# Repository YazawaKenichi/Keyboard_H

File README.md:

# Keyboard_H
This is My First Keyboard Project.

#### 基板とシャーシのデータの完全形
これらのデータで発注・加工する。

#### 自作キーボードの設計
このリポジトリは自作キーボードのためのリポジトリ。
ただしハードウェア設計に関するファイルのみ。うｐ主のインフラの事情的に、ハードは Windows ソフトは Ubuntu で開発することになってしまったので、ハードとソフトでリポジトリを分けた。
統合してぇなぁ...

### 以下全部自己満メモ！自分用れどめ！

##### LED の点灯回路について考える
- USB バスパワー:5V 500mA
- Raspberry Pi Pico の GPIO のパワー
- Raspberry Pi Pico のピンによる電気特性は [RP2040 のデータシート](https://datasheets.raspberrypi.org/rp2040/rp2040-datasheet.pdf) 『5.2.3. Pin Specifications』を参照
- .
- キーボード全体で 300mA になるようにしたい。
- USB 5V だが、実際 500 mA くらい使用すると 4.8V くらいに下がってしまうので、USB デバイスはそうならないように余裕を持たせて設計する。
- GPIO で FET のゲートを制御し、Vbus からの電力を供給する。
- LED と制限抵抗は必ず一つにまとめる。
- .
- 謎があって、USB から電力を入手するとしても、87 個の LED を並列に点灯させようとすると、一つの 抵抗 + LED に流せる電流は最大でも 300 mA / 87 個 ≒ 3.4 mA となってちょっと弱すぎじゃね？って感じがしてしまう。これじゃあ LED 点灯できないじゃん...
- .
- LED のデータシート？これ何？
- output current 出力の最大値 MAX 100 mA
- current limit 制限電流 MIN 150 mA TYP 350 mA MAX 450 mA
- .
- LED の設定
- 一つの LED に電流制限可変抵抗と LED を直列に繋いだ回路において、デューティー比 100% という条件で以下の状態を記録。
- 電源電圧 5 V
- 抵抗降下電圧 1.692 V
- LED 電圧 3.17 V
- 電流 19.30 mA
- 抵抗値 84.5 Ω
- ※小数点以下一桁目より下は当てにならないかも... 0.1 レベルなら当てになるかも。
- 上記が丁度よい輝度になっている。
- .
- 参考までに、電源電圧 3.3 V の時の値も記録しておく。
- 抵抗降下電圧 0.267 V
- LED 電圧 3.03 V
- 電流 10.58 mA
- 抵抗値 21.2 Ω
- ※小数点以下一桁目より下はry
- .
- ついでのついでに参考として、データシートの値を記録しておく。
- デューティー比 100% 電流値  30 mA
- デューティー比 10 % 電流値 100 mA
- 20 mA の時の LED 電圧降下 3.1 V
- .
- 疑問点
- PWM 制御すれば、デューティー比 100 % の時よりも大きな電流を流せるということはわかるけど、推奨デューティー比が 1/10 とかになってて、結局欲しい輝度に届かなくなったりしないのかな？
- Arduino でいいから実験してみると良いかもしれない。
- .
- FET + PWM で実験してみた。
- Nch MOSFET 2N7000 で実験したので、回路的にはローサイド駆動。
- 電流制限抵抗 45Ω PWM: 20ms(50Hz) 100% において、以下を記録。
- 電流 30 mA LED 降下電圧 3.5 V 抵抗降下電圧 1.46 V 但し、100% では僅かに発熱したため、100% 以下での駆動を推奨する。
- .
- なんかもうぐちゃぐちゃしてきたから、いっそのこと実験して特性曲線を自分でプロットすればいいんじゃないかと思って、特性曲線を描いてみた。いや、厳密には点を打っていっただけなんだけど...
- そのスプレッドシートが[こちら](https://docs.google.com/spreadsheets/d/14N7y58BiVdMig64xLq-WeDRAnExjTIeJXDbpEm-JDAk/edit?usp=sharing)
- .
- PWM 制御について参考にしたサイトと数式（自作）
- [PWM について考える基礎](https://www.sist.ac.jp/club/mcf/Umeta_lecture/PWM.html)
- [上記サイト内で出てくる数式](https://www.geogebra.org/m/sed2b5tw) y が電力 x が電流 r が制限抵抗 v が電源電圧。回路は 電源-抵抗-対象素子-GND
- .
- いろいろ考えたけど、USB 電源である以上、最大 500 mA で、しかも余裕を持たせないといけないから 300 mA にしないといけないことも考慮して、一つの 抵抗-LED に流せる電流を考えたら、3.5 mA が限界なわけで、結局 3.5 mA 流すことになるならそれで考えたら良いのではないかという結論に至った。
- Vbus-可変抵抗-LED-[D]NchMOSFET(ON)-[S]GND[G]330Ωカーボン抵抗-3V3PWM の回路において、PWM 100% かつ LED 電流 3.5 の時、630Ω の電流制限抵抗がいい感じ。

##### FET のゲート抵抗について考える
- ゲート抵抗が無いと FET が ON になったときにショートしてしまう。よってゲート抵抗は必要。
- ではゲート抵抗はどのくらいが良いのか。実は計算する方法がある。
- R_G = V_in / I_G ∩ I_G = Q_g / t で求めることができる。
|記号|意味|
|---|---|
|R_G|ゲート抵抗|
|V_in|入力電圧|
|I_G|ゲート電流|
|Q_g|ゲート入力電荷量|
|t|ゲート立ち上がり時間|
- ここで、入力電圧はゲート抵抗への入力電圧であり、ゲート抵抗を超えた時のゲート電圧とは違う。（つまりゲート抵抗で電圧降下する前の電圧ということ）
- ゲート入力電荷量は、使用する FET のデータシートに記載されている。
- 2N7002 のデータシート見てみたけど、書いてない...今回は 100R でいいんじゃね？

##### 教わったこと
- LED のみを安直に並列に接続してはいけない。一つの LED に対して一つの電流制限抵抗が必要となる。よって LED を並列に接続したいときは電流制限抵抗 + LED で一つの素子として考えたほうがいいかもしれない。
- USB の電力は 5V 500 mA である。しかし、デバイスが 500 mA 近く流れそうになると実際は 5 V より少し小さい値に低下してしまう。これを防ぐためにデバイスに流れる電流は 300 mA 程度とし、余裕を持たせたほうが良い。
- FET のゲート抵抗は計算できる。
- FET の G-S 間には 10kR の抵抗をつなぐとよいことを知った。これは MOSFET が OFF の時確実にゲートを OFF にする目的。抵抗が無いと、G-S 間の疑似コンデンサに電荷がたまった状態で、電位は 0V にならず、浮遊状態となり、基準電位を失ってしまう。結果的にゲートの電位が不安定になり FET を ON にしていないにも関わらず勝手に ON になってしまうことが起きてしまう。
- USB 端子に直接つながっている Vbus 端子には、コンデンサがあるとよい。USB 機器のコードは長く、電圧が降下してしまうので、それを防ぐ意味でコンデンサを Vbus GND 間に取り付ける。ただし今回は PWM 制御することを考えるので、電気容量についても注意する必要がある。井口先輩は考えた末に「勘だけど 20 ~ 47 uF」と言っていた。
- ベタグランドはただやたらめったら面積を広くすればよいというものではなく、ベタグランドがアンテナになってしまうときは、敢えて面積を小さくしてでもベタ GND を除去する必要がある。どうしても除去したくない場合は、裏面のベタグランドにビアを繋ぐことで回避できる。
- 配線幅は電流に応じて変更したほうが良い。というかしろ。

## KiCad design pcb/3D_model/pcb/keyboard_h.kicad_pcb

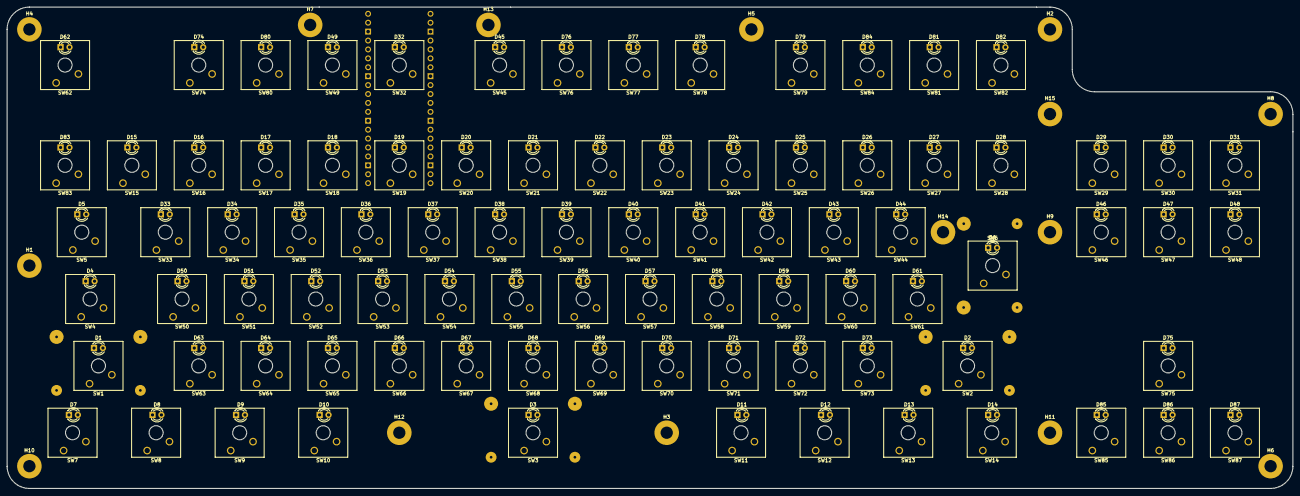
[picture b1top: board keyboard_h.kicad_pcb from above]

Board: 2 copper layers, 366.4 x 137.2 mm, 190 parts (1 on the bottom side), 87 nets, no tracks yet.

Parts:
D1, D2, D3, D4, D5, D6, D7, D8, D9, D10, D11, D12, D13, D14, D15, D16, D17, D18, D19, D20, D21, D22, D23, D24, D25, D26, D27, D28, D29, D30, D31, D32, D33, D34, D35, D36, D37, D38, D39, D40, D41, D42, D43, D44, D45, D46, D47, D48, D49, D50, D51, D52, D53, D54, D55, D56, D57, D58, D59, D60, D61, D62, D63, D64, D65, D66, D67, D68, D69, D70, D71, D72, D73, D74, D75, D76, D77, D78, D79, D80, D81, D82, D83, D84, D85, D86, D87: LED; LED_D3.0mm
H1, H2, H3, H4, H5, H6, H7, H8, H9, H10, H11, H12, H13, H14, H15: MountingHole; MountingHole_3.5mm_Pad
SW1, SW2, SW3: SW_MEC_5G; SW_Cherry_MX_2.00u_Plate
SW4: SW_MEC_5G; SW_Cherry_MX_1.75u_Plate
SW5: SW_MEC_5G; SW_Cherry_MX_1.50u_Plate
SW6: SW_MEC_5G; SW_Cherry_MX_ISOEnter_Plate
SW7, SW8, SW9, SW10, SW11, SW12, SW13, SW14: SW_MEC_5G; SW_Cherry_MX_1.25u_Plate
SW15, SW16, SW17, SW18, SW19, SW20, SW21, SW22, SW23, SW24, SW25, SW26, SW27, SW28, SW29, SW30, SW31, SW32, SW33, SW34, SW35, SW36, SW37, SW38, SW39, SW40, SW41, SW42, SW43, SW44, SW45, SW46, SW47, SW48, SW49, SW50, SW51, SW52, SW53, SW54, SW55, SW56, SW57, SW58, SW59, SW60, SW61, SW62, SW63, SW64, SW65, SW66, SW67, SW68, SW69, SW70, SW71, SW72, SW73, SW74, SW75, SW76, SW77, SW78, SW79, SW80, SW81, SW82, SW83, SW84, SW85, SW86, SW87: SW_MEC_5G; SW_Cherry_MX_1.00u_Plate
U1: Pico; RPi_Pico_SMD_TH

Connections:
unnamed: SW1.1, SW1.2
unnamed: SW2.1, SW2.2
unnamed: SW3.1, SW3.2
unnamed: SW4.1, SW4.2
unnamed: SW5.1, SW5.2
unnamed: SW6.1, SW6.2
unnamed: SW7.1, SW7.2
unnamed: SW8.1, SW8.2
unnamed: SW9.1, SW9.2
unnamed: SW10.1, SW10.2
unnamed: SW11.1, SW11.2
unnamed: SW12.1, SW12.2
unnamed: SW13.1, SW13.2
unnamed: SW14.1, SW14.2
unnamed: SW15.1, SW15.2
unnamed: SW16.1, SW16.2
unnamed: SW17.1, SW17.2
unnamed: SW18.1, SW18.2
unnamed: SW19.1, SW19.2
unnamed: SW20.1, SW20.2
unnamed: SW21.1, SW21.2
unnamed: SW22.1, SW22.2
unnamed: SW23.1, SW23.2
unnamed: SW24.1, SW24.2
unnamed: SW25.1, SW25.2
unnamed: SW26.1, SW26.2
unnamed: SW27.1, SW27.2
unnamed: SW28.1, SW28.2
unnamed: SW29.1, SW29.2
unnamed: SW30.1, SW30.2
unnamed: SW31.1, SW31.2
unnamed: SW32.1, SW32.2
unnamed: SW33.1, SW33.2
unnamed: SW34.1, SW34.2
unnamed: SW35.1, SW35.2
unnamed: SW36.1, SW36.2
unnamed: SW37.1, SW37.2
unnamed: SW38.1, SW38.2
unnamed: SW39.1, SW39.2
unnamed: SW40.1, SW40.2
unnamed: SW41.1, SW41.2
unnamed: SW42.1, SW42.2
unnamed: SW43.1, SW43.2
unnamed: SW44.1, SW44.2
unnamed: SW45.1, SW45.2
unnamed: SW46.1, SW46.2
unnamed: SW47.1, SW47.2
unnamed: SW48.1, SW48.2
unnamed: SW49.1, SW49.2
unnamed: SW50.1, SW50.2
unnamed: SW51.1, SW51.2
unnamed: SW52.1, SW52.2
unnamed: SW53.1, SW53.2
unnamed: SW54.1, SW54.2
unnamed: SW55.1, SW55.2
unnamed: SW56.1, SW56.2
unnamed: SW57.1, SW57.2
unnamed: SW58.1, SW58.2
unnamed: SW59.1, SW59.2
unnamed: SW60.1, SW60.2
unnamed: SW61.1, SW61.2
unnamed: SW62.1, SW62.2
unnamed: SW63.1, SW63.2
unnamed: SW64.1, SW64.2
unnamed: SW65.1, SW65.2
unnamed: SW66.1, SW66.2
unnamed: SW67.1, SW67.2
unnamed: SW68.1, SW68.2
unnamed: SW69.1, SW69.2
unnamed: SW70.1, SW70.2
unnamed: SW71.1, SW71.2
unnamed: SW72.1, SW72.2
unnamed: SW73.1, SW73.2
unnamed: SW74.1, SW74.2
unnamed: SW75.1, SW75.2
unnamed: SW76.1, SW76.2
unnamed: SW77.1, SW77.2
unnamed: SW78.1, SW78.2
unnamed: SW79.1, SW79.2
unnamed: SW80.1, SW80.2
unnamed: SW81.1, SW81.2
unnamed: SW82.1, SW82.2
unnamed: SW83.1, SW83.2
unnamed: SW84.1, SW84.2
unnamed: SW85.1, SW85.2
unnamed: SW86.1, SW86.2
unnamed: SW87.1, SW87.2

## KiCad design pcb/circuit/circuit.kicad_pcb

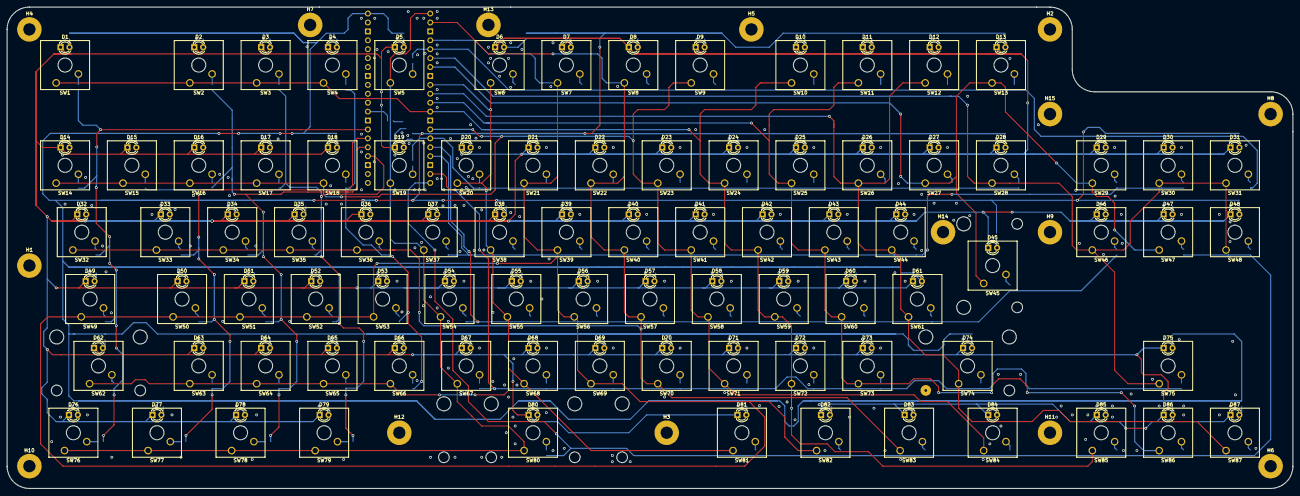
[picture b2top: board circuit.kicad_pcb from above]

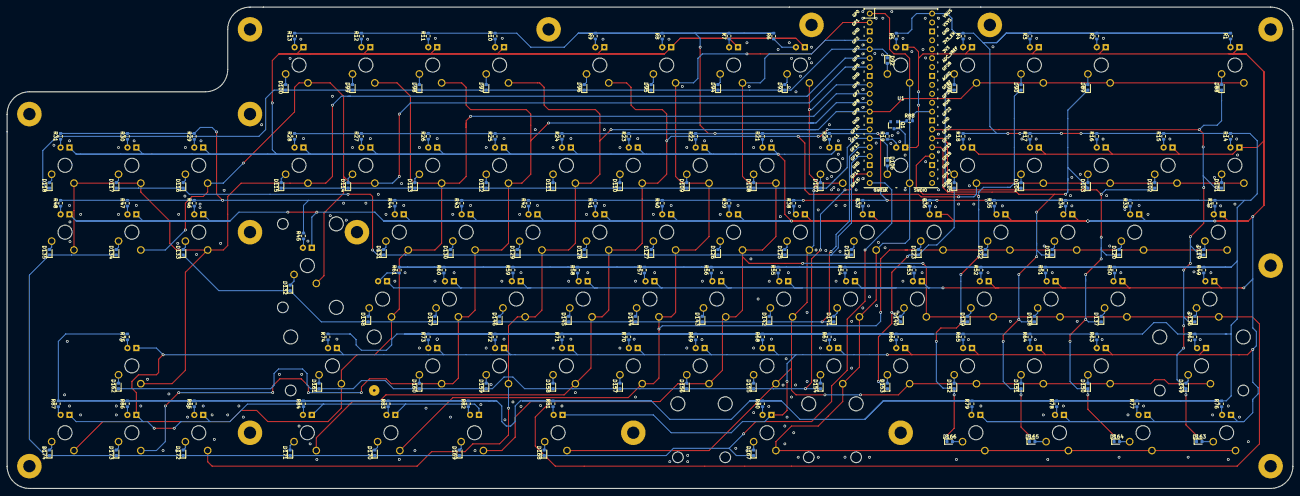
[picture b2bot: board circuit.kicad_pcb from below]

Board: 2 copper layers, 366.4 x 137.2 mm, 366 parts (177 on the bottom side), 200 nets.

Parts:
D1, D2, D3, D4, D5, D6, D7, D8, D9, D10, D11, D12, D13, D14, D15, D16, D17, D18, D19, D20, D21, D22, D23, D24, D25, D26, D27, D28, D29, D30, D31, D32, D33, D34, D35, D36, D37, D38, D39, D40, D41, D42, D43, D44, D45, D46, D47, D48, D49, D50, D51, D52, D53, D54, D55, D56, D57, D58, D59, D60, D61, D62, D63, D64, D65, D66, D67, D68, D69, D70, D71, D72, D73, D74, D75, D76, D77, D78, D79, D80, D81, D82, D83, D84, D85, D86, D87: LED; LED_D3.0mm
D88, D89, D90, D91, D92, D93, D94, D95, D96, D97, D98, D99, D100, D101, D102, D103, D104, D105, D106, D107, D108, D109, D110, D111, D112, D113, D114, D115, D116, D117, D118, D119, D120, D121, D122, D123, D124, D125, D126, D127, D128, D129, D130, D131, D132, D133, D134, D135, D136, D137, D138, D139, D140, D141, D142, D143, D144, D145, D146, D147, D148, D149, D150, D151, D152, D153, D154, D155, D156, D157, D158, D159, D160, D161, D162, D163, D164, D165, D166, D167, D168, D169, D170, D171, D172, D173, D174: 1N4148; LED_0603_1608Metric
H1, H2, H3, H4, H5, H6, H7, H8, H9, H10, H11, H12, H13, H14, H15: MountingHole; MountingHole_3.5mm_Pad
Q1: 2N7002; SOT-23
R1, R2, R3, R4, R5, R6, R7, R8, R9, R10, R11, R12, R13, R14, R15, R16, R17, R18, R19, R20, R21, R22, R23, R24, R25, R26, R27, R28, R29, R30, R31, R32, R33, R34, R35, R36, R37, R38, R39, R40, R41, R42, R43, R44, R45, R46, R47, R48, R49, R50, R51, R52, R53, R54, R55, R56, R57, R58, R59, R60, R61, R62, R63, R64, R65, R66, R67, R68, R69, R70, R71, R72, R73, R74, R75, R76, R77, R78, R79, R80, R81, R82, R83, R84, R85, R86, R87: 630; R_0603_1608Metric
R88: 100; R_0603_1608Metric
SW1, SW2, SW3, SW4, SW5, SW6, SW7, SW8, SW9, SW10, SW11, SW12, SW13, SW14, SW15, SW16, SW17, SW18, SW19, SW20, SW21, SW22, SW23, SW24, SW25, SW26, SW27, SW28, SW29, SW30, SW31, SW33, SW34, SW35, SW36, SW37, SW38, SW39, SW40, SW41, SW42, SW43, SW44, SW46, SW47, SW48, SW50, SW51, SW52, SW53, SW54, SW55, SW56, SW57, SW58, SW59, SW60, SW61, SW63, SW64, SW65, SW66, SW67, SW68, SW69, SW70, SW71, SW72, SW73, SW75, SW85, SW86, SW87: CherryMX; SW_Cherry_MX_1.00u_PCB
SW32, SW76, SW77, SW78, SW79, SW81, SW82, SW83, SW84: CherryMX; SW_Cherry_MX_1.25u_PCB
SW45: CherryMX; SW_Cherry_MX_ISOEnter_PCB
SW49: CherryMX; SW_Cherry_MX_1.50u_PCB
SW62, SW74: CherryMX; SW_Cherry_MX_1.75u_PCB
SW80: CherryMX; SW_Cherry_MX_2.00u_PCB
U1: Pico; RPi_Pico_SMD_TH

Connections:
Col0: SW5.1, SW19.1, SW37.1, SW54.1, SW67.1, SW76.1, SW77.1, SW78.1, SW79.1, SW80.1, U1.1
Col1: SW6.1, SW20.1, SW38.1, SW55.1, SW62.1, SW63.1, SW64.1, SW65.1, SW66.1, SW68.1, SW81.1, U1.9
Col2: SW7.1, SW21.1, SW39.1, SW49.1, SW50.1, SW51.1, SW52.1, SW53.1, SW56.1, SW69.1, SW82.1, U1.4
Col3: SW8.1, SW22.1, SW32.1, SW33.1, SW34.1, SW35.1, SW36.1, SW40.1, SW57.1, SW70.1, SW83.1, U1.2
Col4: SW9.1, SW14.1, SW15.1, SW16.1, SW17.1, SW18.1, SW23.1, SW41.1, SW58.1, SW71.1, SW84.1, U1.14
Col5: SW1.1, SW2.1, SW3.1, SW4.1, SW10.1, SW24.1, SW42.1, SW59.1, SW72.1, SW85.1, U1.12
Col6: SW11.1, SW25.1, SW43.1, SW60.1, SW73.1, SW86.1, U1.11
Col7: SW12.1, SW26.1, SW44.1, SW61.1, SW74.1, SW87.1, U1.10
Col8: SW13.1, SW27.1, SW29.1, SW45.1, SW47.1, U1.7
Col9: SW28.1, SW30.1, SW31.1, SW46.1, SW48.1, SW75.1, U1.6
GND: Q1.2, U1.3, U1.8, U1.13, U1.18, U1.23, U1.28, U1.33, U1.38
unnamed: D1.1, D2.1, D3.1, D4.1, D5.1, D6.1, D7.1, D8.1, D9.1, D10.1, D11.1, D12.1, D13.1, D14.1, D15.1, D16.1, D17.1, D18.1, D19.1, D20.1, D21.1, D22.1, D23.1, D24.1, D25.1, D26.1, D27.1, D28.1, D29.1, D30.1, D31.1, D32.1, D33.1, D34.1, D35.1, D36.1, D37.1, D38.1, D39.1, D40.1, D41.1, D42.1, D43.1, D44.1, D45.1, D46.1, D47.1, D48.1, D49.1, D50.1, D51.1, D52.1, D53.1, D54.1, D55.1, D56.1, D57.1, D58.1, D59.1, D60.1, D61.1, D62.1, D63.1, D64.1, D65.1, D66.1, D67.1, D68.1, D69.1, D70.1, D71.1, D72.1, D73.1, D74.1, D75.1, D76.1, D77.1, D78.1, D79.1, D80.1, D81.1, D82.1, D83.1, D84.1, D85.1, D86.1, D87.1, Q1.3
unnamed: D1.2, R1.1
unnamed: D2.2, R2.1
unnamed: D3.2, R3.1
unnamed: D4.2, R4.1
unnamed: D5.2, R5.1
unnamed: D6.2, R6.1
unnamed: D7.2, R7.1
unnamed: D8.2, R8.1
unnamed: D9.2, R9.1
unnamed: D10.2, R10.1
unnamed: D11.2, R11.1
unnamed: D12.2, R12.1
unnamed: D13.2, R13.1
unnamed: D14.2, R14.1
unnamed: D15.2, R15.1
unnamed: D16.2, R16.1
unnamed: D17.2, R17.1
unnamed: D18.2, R18.1
unnamed: D19.2, R19.1
unnamed: D20.2, R20.1
unnamed: D21.2, R21.1
unnamed: D22.2, R22.1
unnamed: D23.2, R23.1
unnamed: D24.2, R24.1
unnamed: D25.2, R25.1
unnamed: D26.2, R26.1
unnamed: D27.2, R27.1
unnamed: D28.2, R28.1
unnamed: D29.2, R29.1
unnamed: D30.2, R30.1
unnamed: D31.2, R31.1
unnamed: D32.2, R32.1
unnamed: D33.2, R33.1
unnamed: D34.2, R34.1
unnamed: D35.2, R35.1
unnamed: D36.2, R36.1
unnamed: D37.2, R37.1
unnamed: D38.2, R38.1
unnamed: D39.2, R39.1
unnamed: D40.2, R40.1
unnamed: D41.2, R41.1
unnamed: D42.2, R42.1
unnamed: D43.2, R43.1
unnamed: D44.2, R44.1
unnamed: D45.2, R45.1
unnamed: D46.2, R46.1
unnamed: D47.2, R47.1
unnamed: D48.2, R48.1
unnamed: D49.2, R49.1
unnamed: D50.2, R50.1
unnamed: D51.2, R51.1
unnamed: D52.2, R52.1
unnamed: D53.2, R53.1
unnamed: D54.2, R54.1
unnamed: D55.2, R55.1
unnamed: D56.2, R56.1
unnamed: D57.2, R57.1
unnamed: D58.2, R58.1
unnamed: D59.2, R59.1
unnamed: D60.2, R60.1
unnamed: D61.2, R61.1
unnamed: D62.2, R62.1
unnamed: D63.2, R63.1
unnamed: D64.2, R64.1
unnamed: D65.2, R65.1
unnamed: D66.2, R66.1
unnamed: D67.2, R67.1
unnamed: D68.2, R68.1
unnamed: D69.2, R69.1
unnamed: D70.2, R70.1
unnamed: D71.2, R71.1
unnamed: D72.2, R72.1
unnamed: D73.2, R73.1
unnamed: D74.2, R74.1
unnamed: D75.2, R75.1
unnamed: D76.2, R76.1
unnamed: D77.2, R77.1
unnamed: D78.2, R78.1
unnamed: D79.2, R79.1
unnamed: D80.2, R80.1
unnamed: D81.2, R81.1
unnamed: D82.2, R82.1
unnamed: D83.2, R83.1
unnamed: D84.2, R84.1
unnamed: D85.2, R85.1
unnamed: D86.2, R86.1
unnamed: D87.2, R87.1
unnamed: D88.2, SW1.2
unnamed: D89.2, SW2.2
unnamed: D90.2, SW3.2
unnamed: D91.2, SW4.2
unnamed: D92.2, SW5.2
unnamed: D93.2, SW6.2
unnamed: D94.2, SW7.2
unnamed: D95.2, SW8.2
unnamed: D96.2, SW9.2
unnamed: D97.2, SW10.2
unnamed: D98.2, SW11.2
unnamed: D99.2, SW12.2
unnamed: D100.2, SW13.2
unnamed: D101.2, SW14.2
unnamed: D102.2, SW15.2
unnamed: D103.2, SW16.2
unnamed: D104.2, SW17.2
unnamed: D91.1, D105.1, D123.1, D140.1, D153.1
unnamed: D105.2, SW18.2
unnamed: D106.2, SW19.2
unnamed: D107.2, SW20.2
unnamed: D108.2, SW21.2
unnamed: D109.2, SW22.2
unnamed: D110.2, SW23.2
unnamed: D111.2, SW24.2
unnamed: D112.2, SW25.2
unnamed: D113.2, SW26.2
unnamed: D114.2, SW27.2
unnamed: D115.2, SW28.2
unnamed: D116.2, SW29.2
unnamed: D117.2, SW30.2
unnamed: D118.2, SW31.2
unnamed: D119.2, SW32.2
unnamed: D120.2, SW33.2
unnamed: D121.2, SW34.2
unnamed: D122.2, SW35.2
unnamed: D123.2, SW36.2
unnamed: D124.2, SW37.2
unnamed: D125.2, SW38.2
unnamed: D126.2, SW39.2
unnamed: D127.2, SW40.2
unnamed: D128.2, SW41.2
unnamed: D129.2, SW42.2
unnamed: D130.2, SW43.2
unnamed: D131.2, SW44.2
unnamed: D132.2, SW45.2
unnamed: D133.2, SW46.2
unnamed: D134.2, SW47.2
unnamed: D135.2, SW48.2
unnamed: D136.2, SW49.2
unnamed: D137.2, SW50.2
unnamed: D138.2, SW51.2
unnamed: D139.2, SW52.2
unnamed: D140.2, SW53.2
unnamed: D141.2, SW54.2
unnamed: D142.2, SW55.2
unnamed: D143.2, SW56.2
unnamed: D144.2, SW57.2
unnamed: D145.2, SW58.2
unnamed: D146.2, SW59.2
unnamed: D147.2, SW60.2
unnamed: D148.2, SW61.2
unnamed: D149.2, SW62.2
unnamed: D150.2, SW63.2
unnamed: D151.2, SW64.2
unnamed: D152.2, SW65.2
unnamed: D153.2, SW66.2
unnamed: D154.2, SW67.2
unnamed: D155.2, SW68.2
unnamed: D156.2, SW69.2
unnamed: D157.2, SW70.2
unnamed: D158.2, SW71.2
unnamed: D159.2, SW72.2
unnamed: D160.2, SW73.2
unnamed: D161.2, SW74.2
unnamed: D162.2, SW75.2
unnamed: D163.2, SW76.2
unnamed: D164.2, SW77.2
unnamed: D165.2, SW78.2
unnamed: D166.2, SW79.2
unnamed: D167.2, SW80.2
unnamed: D168.2, SW81.2
unnamed: D169.2, SW82.2
unnamed: D170.2, SW83.2
unnamed: D171.2, SW84.2
unnamed: D172.2, SW85.2
unnamed: D173.2, SW86.2
unnamed: D174.2, SW87.2
unnamed: Q1.1, R88.1
PWM: R88.2, U1.29
Row0: D92.1, D93.1, D94.1, D95.1, D96.1, D97.1, D98.1, D99.1, D100.1, D118.1, U1.5
Row1: D106.1, D107.1, D108.1, D109.1, D110.1, D111.1, D112.1, D113.1, D114.1, D115.1, U1.15
Row2: D116.1, D117.1, D124.1, D125.1, D126.1, D127.1, D128.1, D129.1, D130.1, D131.1, U1.17
Row3: D132.1, D133.1, D141.1, D142.1, D143.1, D144.1, D145.1, D146.1, D147.1, D148.1, U1.16
Row4: D154.1, D155.1, D156.1, D157.1, D158.1, D159.1, D160.1, D161.1, D162.1, U1.19
Row5: D134.1, D135.1, D167.1, D168.1, D169.1, D170.1, D171.1, D172.1, D173.1, D174.1, U1.20
Row6: D88.1, D101.1, D119.1, D136.1, D149.1, D163.1, U1.27
Row7: D102.1, D120.1, D137.1, D150.1, D164.1, U1.26
Row8: D89.1, D103.1, D121.1, D138.1, D151.1, D165.1, U1.25
Row9: D90.1, D104.1, D122.1, D139.1, D152.1, D166.1, U1.24
VBUS: R1.2, R2.2, R3.2, R4.2, R5.2, R6.2, R7.2, R8.2, R9.2, R10.2, R11.2, R12.2, R13.2, R14.2, R15.2, R16.2, R17.2, R18.2, R19.2, R20.2, R21.2, R22.2, R23.2, R24.2, R25.2, R26.2, R27.2, R28.2, R29.2, R30.2, R31.2, R32.2, R33.2, R34.2, R35.2, R36.2, R37.2, R38.2, R39.2, R40.2, R41.2, R42.2, R43.2, R44.2, R45.2, R46.2, R47.2, R48.2, R49.2, R50.2, R51.2, R52.2, R53.2, R54.2, R55.2, R56.2, R57.2, R58.2, R59.2, R60.2, R61.2, R62.2, R63.2, R64.2, R65.2, R66.2, R67.2, R68.2, R69.2, R70.2, R71.2, R72.2, R73.2, R74.2, R75.2, R76.2, R77.2, R78.2, R79.2, R80.2, R81.2, R82.2, R83.2, R84.2, R85.2, R86.2, R87.2, U1.40

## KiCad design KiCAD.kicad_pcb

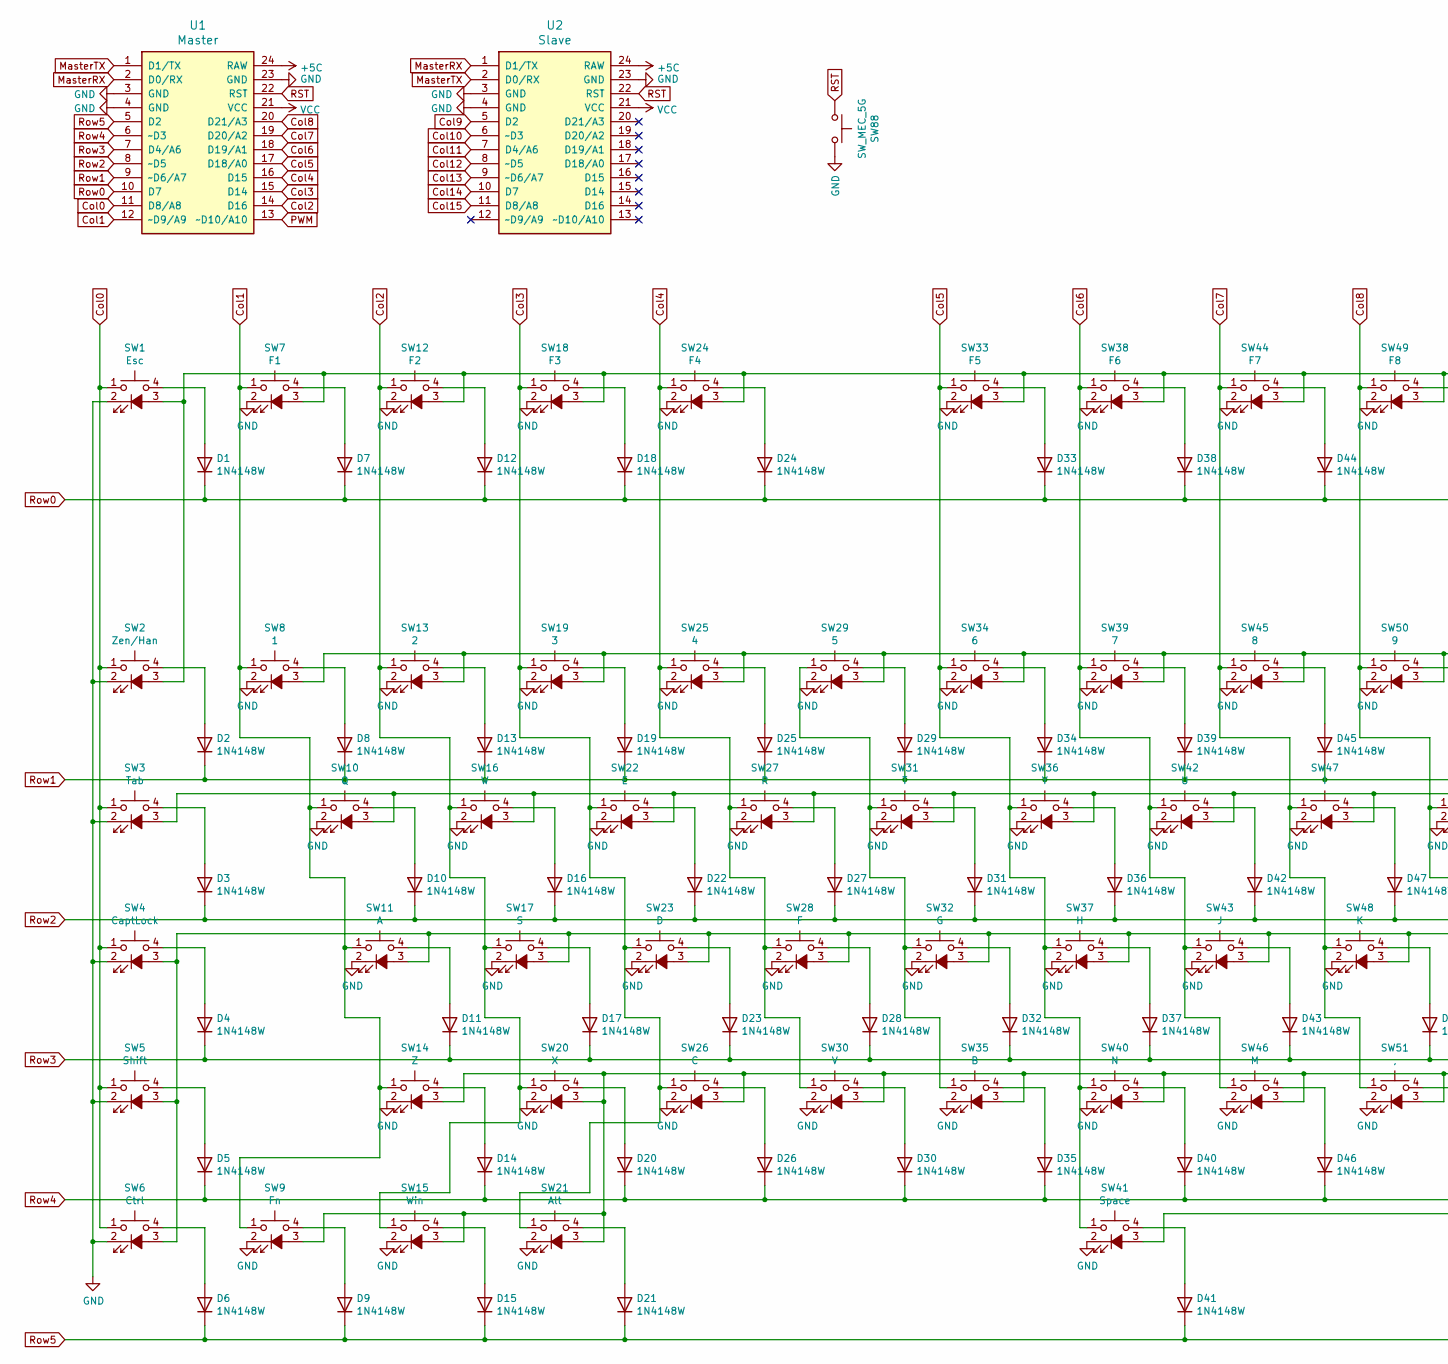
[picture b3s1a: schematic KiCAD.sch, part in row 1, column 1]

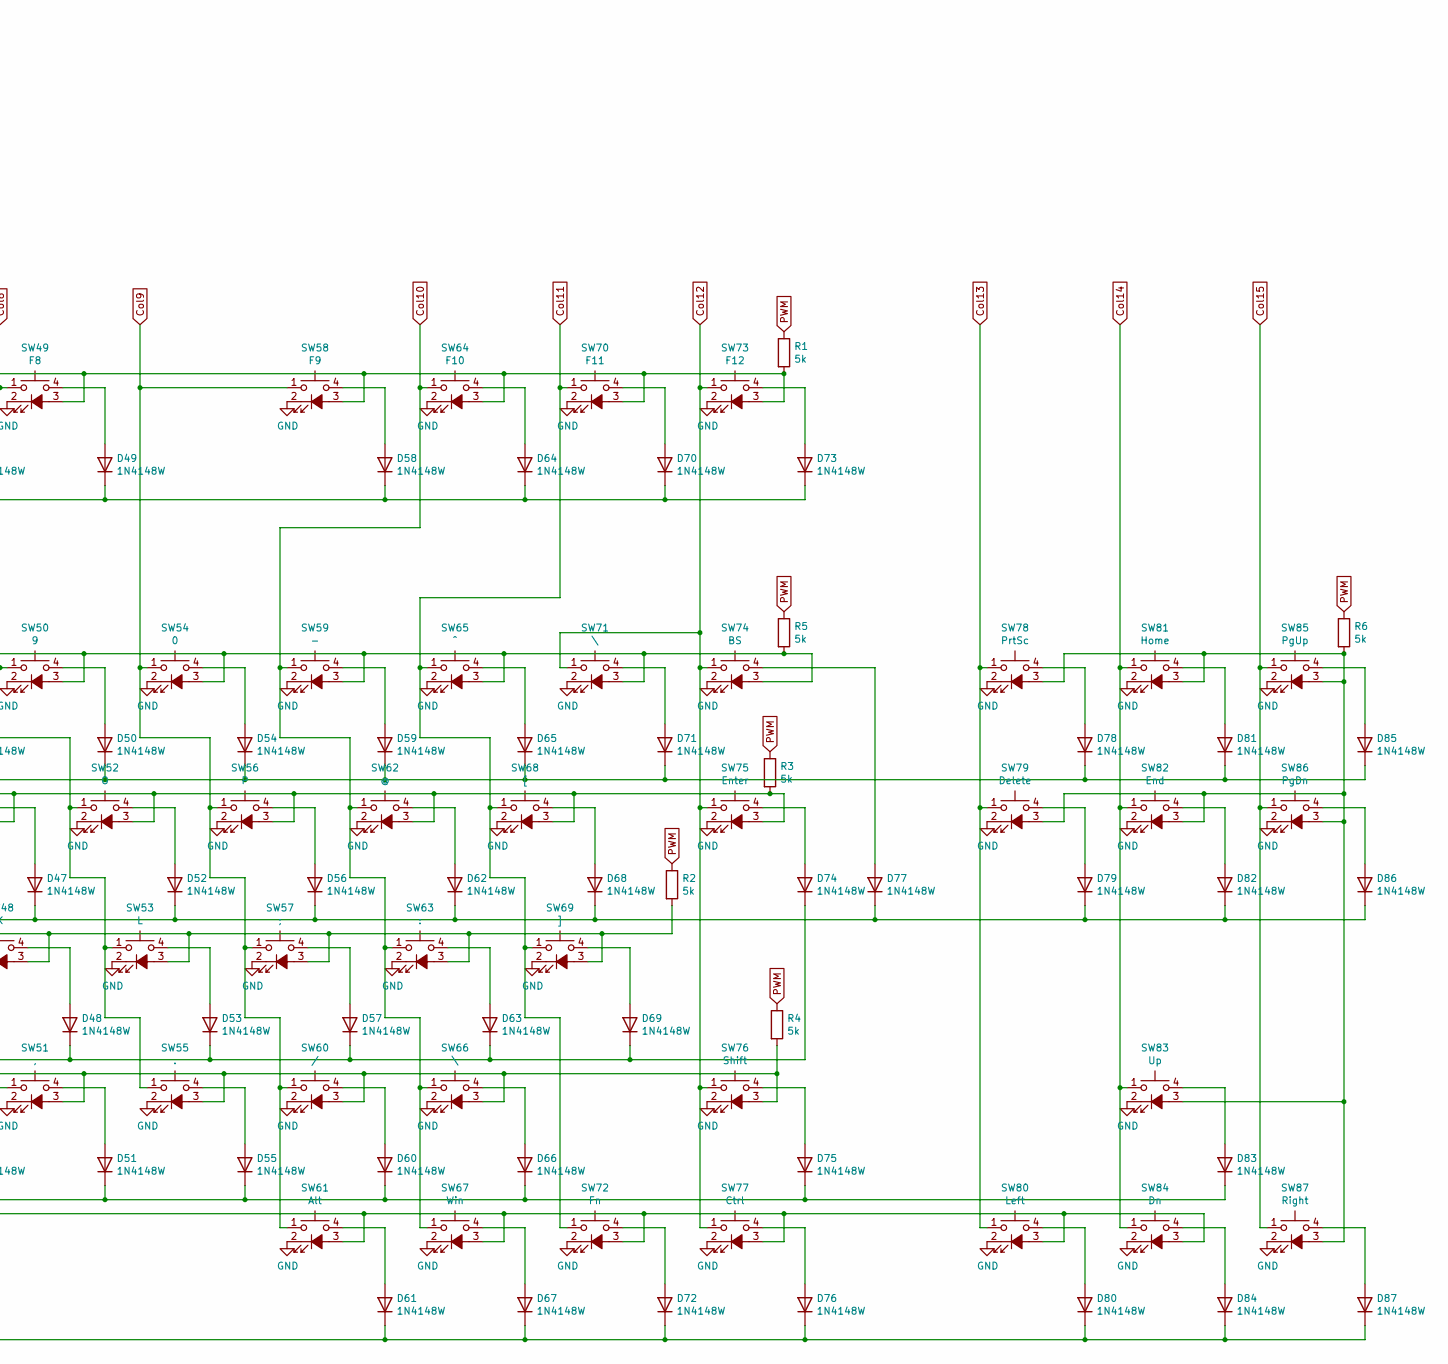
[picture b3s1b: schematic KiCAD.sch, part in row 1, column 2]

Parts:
D1, D2, D3, D4, D5, D6, D7, D8, D9, D10, D11, D12, D13, D14, D15, D16, D17, D18, D19, D20, D21, D22, D23, D24, D25, D26, D27, D28, D29, D30, D31, D32, D33, D34, D35, D36, D37, D38, D39, D40, D41, D42, D43, D44, D45, D46, D47, D48, D49, D50, D51, D52, D53, D54, D55, D56, D57, D58, D59, D60, D61, D62, D63, D64, D65, D66, D67, D68, D69, D70, D71, D72, D73, D74, D75, D76, D77, D78, D79, D80, D81, D82, D83, D84, D85, D86, D87: 1N4148W; D_SOD-123
R1, R2, R3, R4, R5, R6: 5k; R_0603_1608Metric
SW1: Esc; SW_Cherry_MX_1.00u_Plate
SW2: Zen/Han; SW_Cherry_MX_1.00u_Plate
SW3: Tab; SW_Cherry_MX_1.50u_Plate
SW4: CaptLock; SW_Cherry_MX_1.75u_Plate
SW5: Shift; SW_Cherry_MX_2.00u_Plate
SW6, SW77: Ctrl; SW_Cherry_MX_1.25u_Plate
SW7: F1; SW_Cherry_MX_1.00u_Plate
SW8: 1; SW_Cherry_MX_1.00u_Plate
SW9, SW72: Fn; SW_Cherry_MX_1.25u_Plate
SW10: Q; SW_Cherry_MX_1.00u_Plate
SW11: A; SW_Cherry_MX_1.00u_Plate
SW12: F2; SW_Cherry_MX_1.00u_Plate
SW13: 2; SW_Cherry_MX_1.00u_Plate
SW14: Z; SW_Cherry_MX_1.00u_Plate
SW15: Win; SW_Cherry_MX_1.50u_Plate
SW16: W; SW_Cherry_MX_1.00u_Plate
SW17: S; SW_Cherry_MX_1.00u_Plate
SW18: F3; SW_Cherry_MX_1.00u_Plate
SW19: 3; SW_Cherry_MX_1.00u_Plate
SW20: X; SW_Cherry_MX_1.00u_Plate
SW21, SW61: Alt; SW_Cherry_MX_1.25u_Plate
SW22: E; SW_Cherry_MX_1.00u_Plate
SW23: D; SW_Cherry_MX_1.00u_Plate
SW24: F4; SW_Cherry_MX_1.00u_Plate
SW25: 4; SW_Cherry_MX_1.00u_Plate
SW26: C; SW_Cherry_MX_1.00u_Plate
SW27: R; SW_Cherry_MX_1.00u_Plate
SW28: F; SW_Cherry_MX_1.00u_Plate
SW29: 5; SW_Cherry_MX_1.00u_Plate
SW30: V; SW_Cherry_MX_1.00u_Plate
SW31: T; SW_Cherry_MX_1.00u_Plate
SW32: G; SW_Cherry_MX_1.00u_Plate
SW33: F5; SW_Cherry_MX_1.00u_Plate
SW34: 6; SW_Cherry_MX_1.00u_Plate
SW35: B; SW_Cherry_MX_1.00u_Plate
SW36: Y; SW_Cherry_MX_1.00u_Plate
SW37: H; SW_Cherry_MX_1.00u_Plate
SW38: F6; SW_Cherry_MX_1.00u_Plate
SW39: 7; SW_Cherry_MX_1.00u_Plate
SW40: N; SW_Cherry_MX_1.00u_Plate
SW41: Space; SW_Cherry_MX_1.75u_Plate
SW42: U; SW_Cherry_MX_1.00u_Plate
SW43: J; SW_Cherry_MX_1.00u_Plate
SW44: F7; SW_Cherry_MX_1.00u_Plate
SW45: 8; SW_Cherry_MX_1.00u_Plate
SW46: M; SW_Cherry_MX_1.00u_Plate
SW47: I; SW_Cherry_MX_1.00u_Plate
SW48: K; SW_Cherry_MX_1.00u_Plate
SW49: F8; SW_Cherry_MX_1.00u_Plate
SW50: 9; SW_Cherry_MX_1.00u_Plate
SW51: ,; SW_Cherry_MX_1.00u_Plate
SW52: O; SW_Cherry_MX_1.00u_Plate
SW53: L; SW_Cherry_MX_1.00u_Plate
SW54: 0; SW_Cherry_MX_1.00u_Plate
SW55: .; SW_Cherry_MX_1.00u_Plate
SW56: P; SW_Cherry_MX_1.00u_Plate
SW57: ;; SW_Cherry_MX_1.00u_Plate
SW58: F9; SW_Cherry_MX_1.00u_Plate
SW59: -; SW_Cherry_MX_1.00u_Plate
SW60: /; SW_Cherry_MX_1.00u_Plate
SW62: @; SW_Cherry_MX_1.00u_Plate
SW63: :; SW_Cherry_MX_1.00u_Plate
SW64: F10; SW_Cherry_MX_1.00u_Plate
SW65: ^; SW_Cherry_MX_1.00u_Plate
SW66, SW71: \\; SW_Cherry_MX_1.00u_Plate
SW67: Win; SW_Cherry_MX_1.25u_Plate
SW68: [; SW_Cherry_MX_1.00u_Plate
SW69: ]; SW_Cherry_MX_1.00u_Plate
SW70: F11; SW_Cherry_MX_1.00u_Plate
SW73: F12; SW_Cherry_MX_1.00u_Plate
SW74: BS; SW_Cherry_MX_1.00u_Plate
SW75: Enter; SW_Cherry_MX_ISOEnter_Plate
SW76: Shift; SW_Cherry_MX_1.75u_Plate
SW78: PrtSc; SW_Cherry_MX_1.00u_Plate
SW79: Delete; SW_Cherry_MX_1.00u_Plate
SW80: Left; SW_Cherry_MX_1.00u_Plate
SW81: Home; SW_Cherry_MX_1.00u_Plate
SW82: End; SW_Cherry_MX_1.00u_Plate
SW83: Up; SW_Cherry_MX_1.00u_Plate
SW84: Dn; SW_Cherry_MX_1.00u_Plate
SW85: PgUp; SW_Cherry_MX_1.00u_Plate
SW86: PgDn; SW_Cherry_MX_1.00u_Plate
SW87: Right; SW_Cherry_MX_1.00u_Plate
SW88: SW_MEC_5G; SW_PUSH_6mm_H5mm
U1: Master; Sparkfun_Pro_Micro
U2: Slave; Sparkfun_Pro_Micro

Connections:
+5C: U1.24 (RAW), U2.24 (RAW)
Col0: SW1.1, SW2.1, SW3.1, SW4.1, SW5.1, SW6.1, U1.11 (D8/A8)
Col1: SW7.1, SW8.1, SW9.1, SW10.1, SW11.1, SW14.1, U1.12 (~~D9/A9)
Col2: SW12.1, SW13.1, SW15.1, SW16.1, SW17.1, SW20.1, U1.14 (D16)
Col3: SW18.1, SW19.1, SW21.1, SW22.1, SW23.1, SW26.1, U1.15 (D14)
Col4: SW24.1, SW25.1, SW27.1, SW28.1, SW30.1, U1.16 (D15)
Col5: SW33.1, SW34.1, SW36.1, SW37.1, SW40.1, SW41.1, U1.17 (D18/A0)
Col6: SW38.1, SW39.1, SW42.1, SW43.1, SW46.1, U1.18 (D19/A1)
Col7: SW44.1, SW45.1, SW47.1, SW48.1, SW51.1, U1.19 (D20/A2)
Col8: SW49.1, SW50.1, SW52.1, SW53.1, SW55.1, U1.20 (D21/A3)
Col9: SW54.1, SW56.1, SW57.1, SW58.1, SW60.1, SW61.1, U2.5 (D2)
Col10: SW59.1, SW62.1, SW63.1, SW64.1, SW66.1, SW67.1, U2.6 (~~D3)
Col11: SW65.1, SW68.1, SW69.1, SW70.1, SW72.1, U2.7 (D4/A6)
Col12: SW71.1, SW73.1, SW74.1, SW75.1, SW76.1, SW77.1, U2.8 (~~D5)
Col13: SW78.1, SW79.1, SW80.1, U2.9 (~~D6/A7)
Col14: SW81.1, SW82.1, SW83.1, SW84.1, U2.10 (D7)
Col15: SW85.1, SW86.1, SW87.1, U2.11 (D8/A8)
GND: SW1.2, SW2.2, SW3.2, SW4.2, SW5.2, SW6.2, SW7.2, SW8.2, SW9.2, SW10.2, SW11.2, SW12.2, SW13.2, SW14.2, SW15.2, SW16.2, SW17.2, SW18.2, SW19.2, SW20.2, SW21.2, SW22.2, SW23.2, SW24.2, SW25.2, SW26.2, SW27.2, SW28.2, SW29.2, SW30.2, SW31.2, SW32.2, SW33.2, SW34.2, SW35.2, SW36.2, SW37.2, SW38.2, SW39.2, SW40.2, SW41.2, SW42.2, SW43.2, SW44.2, SW45.2, SW46.2, SW47.2, SW48.2, SW49.2, SW50.2, SW51.2, SW52.2, SW53.2, SW54.2, SW55.2, SW56.2, SW57.2, SW58.2, SW59.2, SW60.2, SW61.2, SW62.2, SW63.2, SW64.2, SW65.2, SW66.2, SW67.2, SW68.2, SW69.2, SW70.2, SW71.2, SW72.2, SW73.2, SW74.2, SW75.2, SW76.2, SW77.2, SW78.2, SW79.2, SW80.2, SW81.2, SW82.2, SW83.2, SW84.2, SW85.2, SW86.2, SW87.2, SW88.3 (B), SW88.4 (B), U1.3 (GND), U1.4 (GND), U1.23 (GND), U2.3 (GND), U2.4 (GND), U2.23 (GND)
MasterRX: U1.2 (D0/RX), U2.1 (D1/TX)
MasterTX: U1.1 (D1/TX), U2.2 (D0/RX)
unnamed: D1.2 (A), SW1.4 (A)
unnamed: D2.2 (A), SW2.4 (A)
unnamed: D3.2 (A), SW3.4 (A)
unnamed: D4.2 (A), SW4.4 (A)
unnamed: D5.2 (A), SW5.4 (A)
unnamed: D6.2 (A), SW6.4 (A)
unnamed: D7.2 (A), SW7.4 (A)
unnamed: D8.2 (A), SW8.4 (A)
unnamed: D9.2 (A), SW9.4 (A)
unnamed: D10.2 (A), SW10.4 (A)
unnamed: D11.2 (A), SW11.4 (A)
unnamed: D12.2 (A), SW12.4 (A)
unnamed: D13.2 (A), SW13.4 (A)
unnamed: D14.2 (A), SW14.4 (A)
unnamed: D15.2 (A), SW15.4 (A)
unnamed: D16.2 (A), SW16.4 (A)
unnamed: D17.2 (A), SW17.4 (A)
unnamed: D18.2 (A), SW18.4 (A)
unnamed: D19.2 (A), SW19.4 (A)
unnamed: D20.2 (A), SW20.4 (A)
unnamed: D21.2 (A), SW21.4 (A)
unnamed: D22.2 (A), SW22.4 (A)
unnamed: D23.2 (A), SW23.4 (A)
unnamed: D24.2 (A), SW24.4 (A)
unnamed: D25.2 (A), SW25.4 (A)
unnamed: D26.2 (A), SW26.4 (A)
unnamed: D27.2 (A), SW27.4 (A)
unnamed: D28.2 (A), SW28.4 (A)
unnamed: D29.2 (A), SW29.4 (A)
unnamed: D30.2 (A), SW30.4 (A)
unnamed: D31.2 (A), SW31.4 (A)
unnamed: D32.2 (A), SW32.4 (A)
unnamed: D33.2 (A), SW33.4 (A)
unnamed: D34.2 (A), SW34.4 (A)
unnamed: D35.2 (A), SW35.4 (A)
unnamed: D36.2 (A), SW36.4 (A)
unnamed: D37.2 (A), SW37.4 (A)
unnamed: D38.2 (A), SW38.4 (A)
unnamed: D39.2 (A), SW39.4 (A)
unnamed: D40.2 (A), SW40.4 (A)
unnamed: D41.2 (A), SW41.4 (A)
unnamed: D42.2 (A), SW42.4 (A)
unnamed: D43.2 (A), SW43.4 (A)
unnamed: D44.2 (A), SW44.4 (A)
unnamed: D45.2 (A), SW45.4 (A)
unnamed: D46.2 (A), SW46.4 (A)
unnamed: D47.2 (A), SW47.4 (A)
unnamed: D48.2 (A), SW48.4 (A)
unnamed: D49.2 (A), SW49.4 (A)
unnamed: D50.2 (A), SW50.4 (A)
unnamed: D51.2 (A), SW51.4 (A)
unnamed: D52.2 (A), SW52.4 (A)
unnamed: D53.2 (A), SW53.4 (A)
unnamed: D54.2 (A), SW54.4 (A)
unnamed: D55.2 (A), SW55.4 (A)
unnamed: D56.2 (A), SW56.4 (A)
unnamed: D57.2 (A), SW57.4 (A)
unnamed: D58.2 (A), SW58.4 (A)
unnamed: D59.2 (A), SW59.4 (A)
unnamed: D60.2 (A), SW60.4 (A)
unnamed: D61.2 (A), SW61.4 (A)
unnamed: D62.2 (A), SW62.4 (A)
unnamed: D63.2 (A), SW63.4 (A)
unnamed: D64.2 (A), SW64.4 (A)
unnamed: D65.2 (A), SW65.4 (A)
unnamed: D66.2 (A), SW66.4 (A)
unnamed: D67.2 (A), SW67.4 (A)
unnamed: D68.2 (A), SW68.4 (A)
unnamed: D69.2 (A), SW69.4 (A)
unnamed: D70.2 (A), SW70.4 (A)
unnamed: D71.2 (A), SW71.4 (A)
unnamed: D72.2 (A), SW72.4 (A)
unnamed: D73.2 (A), SW73.4 (A)
unnamed: D74.2 (A), SW75.4 (A)
unnamed: D75.2 (A), SW76.4 (A)
unnamed: D76.2 (A), SW77.4 (A)
unnamed: D77.2 (A), SW74.4 (A)
unnamed: D78.2 (A), SW78.4 (A)
unnamed: D79.2 (A), SW79.4 (A)
unnamed: D80.2 (A), SW80.4 (A)
unnamed: D81.2 (A), SW81.4 (A)
unnamed: D82.2 (A), SW82.4 (A)
unnamed: D83.2 (A), SW83.4 (A)
unnamed: D84.2 (A), SW84.4 (A)
unnamed: D85.2 (A), SW85.4 (A)
unnamed: D86.2 (A), SW86.4 (A)
unnamed: D87.2 (A), SW87.4 (A)
unnamed: R1.2, SW1.3 (K), SW2.3 (K), SW7.3 (K), SW12.3 (K), SW18.3 (K), SW24.3 (K), SW33.3 (K), SW38.3 (K), SW44.3 (K), SW49.3 (K), SW58.3 (K), SW64.3 (K), SW70.3 (K), SW73.3 (K)
unnamed: R2.2, SW4.3 (K), SW5.3 (K), SW6.3 (K), SW11.3 (K), SW17.3 (K), SW23.3 (K), SW28.3 (K), SW32.3 (K), SW37.3 (K), SW43.3 (K), SW48.3 (K), SW53.3 (K), SW57.3 (K), SW63.3 (K), SW69.3 (K)
unnamed: R3.2, SW3.3 (K), SW10.3 (K), SW16.3 (K), SW22.3 (K), SW27.3 (K), SW31.3 (K), SW36.3 (K), SW42.3 (K), SW47.3 (K), SW52.3 (K), SW56.3 (K), SW62.3 (K), SW68.3 (K), SW75.3 (K)
unnamed: R4.2, SW9.3 (K), SW14.3 (K), SW15.3 (K), SW20.3 (K), SW21.3 (K), SW26.3 (K), SW30.3 (K), SW35.3 (K), SW40.3 (K), SW46.3 (K), SW51.3 (K), SW55.3 (K), SW60.3 (K), SW66.3 (K), SW76.3 (K)
unnamed: R5.2, SW8.3 (K), SW13.3 (K), SW19.3 (K), SW25.3 (K), SW29.3 (K), SW34.3 (K), SW39.3 (K), SW45.3 (K), SW50.3 (K), SW54.3 (K), SW59.3 (K), SW65.3 (K), SW71.3 (K), SW74.3 (K)
unnamed: R6.2, SW78.3 (K), SW79.3 (K), SW81.3 (K), SW82.3 (K), SW83.3 (K), SW85.3 (K), SW86.3 (K), SW87.3 (K)
unnamed: SW29.1, SW31.1, SW32.1, SW35.1
unnamed: SW41.3 (K), SW61.3 (K), SW67.3 (K), SW72.3 (K), SW77.3 (K), SW80.3 (K), SW84.3 (K)
PWM: R1.1, R2.1, R3.1, R4.1, R5.1, R6.1, U1.13 (~~D10/A10)
RST: SW88.1 (A), SW88.2 (A), U1.22 (RST), U2.22 (RST)
Row0: D1.1 (K), D7.1 (K), D12.1 (K), D18.1 (K), D24.1 (K), D33.1 (K), D38.1 (K), D44.1 (K), D49.1 (K), D58.1 (K), D64.1 (K), D70.1 (K), D73.1 (K), U1.10 (D7)
Row1: D2.1 (K), D8.1 (K), D13.1 (K), D19.1 (K), D25.1 (K), D29.1 (K), D34.1 (K), D39.1 (K), D45.1 (K), D50.1 (K), D54.1 (K), D59.1 (K), D65.1 (K), D71.1 (K), D78.1 (K), D81.1 (K), D85.1 (K), U1.9 (~~D6/A7)
Row2: D3.1 (K), D10.1 (K), D16.1 (K), D22.1 (K), D27.1 (K), D31.1 (K), D36.1 (K), D42.1 (K), D47.1 (K), D52.1 (K), D56.1 (K), D62.1 (K), D68.1 (K), D77.1 (K), D79.1 (K), D82.1 (K), D86.1 (K), U1.8 (~~D5)
Row3: D4.1 (K), D11.1 (K), D17.1 (K), D23.1 (K), D28.1 (K), D32.1 (K), D37.1 (K), D43.1 (K), D48.1 (K), D53.1 (K), D57.1 (K), D63.1 (K), D69.1 (K), D74.1 (K), U1.7 (D4/A6)
Row4: D5.1 (K), D14.1 (K), D20.1 (K), D26.1 (K), D30.1 (K), D35.1 (K), D40.1 (K), D46.1 (K), D51.1 (K), D55.1 (K), D60.1 (K), D66.1 (K), D75.1 (K), D83.1 (K), U1.6 (~~D3)
Row5: D6.1 (K), D9.1 (K), D15.1 (K), D21.1 (K), D41.1 (K), D61.1 (K), D67.1 (K), D72.1 (K), D76.1 (K), D80.1 (K), D84.1 (K), D87.1 (K), U1.5 (D2)
VCC: U1.21 (VCC), U2.21 (VCC)

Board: 2 copper layers, 183 parts (0 on the bottom side), 124 nets, no tracks yet.

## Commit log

2021-08-04 ダイオードを直列から並列に変更
2021-08-05 テンキーを消した。キー軸の上下を逆にした。マイコンを一つ無くした。デバッグ用LEDを無くした。結果PCBnewを作り直すことになった。
2021-08-06 グローバルラベルにした。
2021-08-15 ProMicro
2021-08-16 フットプリントを変えた。
2021-08-17 フットプリント配置中
2021-08-17 改変フットプリントを追加
2021-08-17 キーキャップの寸法を確定させないと何も設計できない
2021-08-18 Push できる？
2021-08-18 PDF を追加
2021-08-26 ツリー構造を変更した
2021-09-01 Ƃ肠¦¸®¬I
2021-09-01 とりあえず完成
2021-09-02 add gerber data
2021-09-02 add gerber data and change file tree
2021-09-05 LED の点灯方法を変更。それぞれの LED に電流制限抵抗を追加。
2021-09-05 シャーシ設計用に 3D モデルだけ出力できるようにもう一つ KiCAD プロジェクトを作った。まだラズパイピコのモデルデータを実装できてない。
2021-09-05 step ファイルを出力した
2021-09-06 Mount Hall の位置を調節した。3D モデルには手を着けてないから使えないよ！
2021-09-06 Inventor で Plate を作った。
2021-09-08 GS間抵抗を追加。G抵抗を追加。なんかスイッチのフットプリント一つ消えちゃった
2021-09-08 復元した
2021-09-09 これからアンテナに気を付けつつベタグランドを追加する
2021-09-09 とりあえず配線幅を太くした。
2021-09-09 配線の横に流れる電流値を記載しておいた。
2021-09-09 ベタグランドの配置途中
2021-09-11 x^Oh̃Aei𖳂­µ½Bzüð0.3mm ɂµ½B
2021-09-12 Plate に支柱を付けた
2021-09-12 これなにした？
2021-09-12 step ファイルの追加
2021-09-12 3D モデルの正投影 PNG を追加
2021-09-14 Plate を少し広くした
2021-09-14 とりあえず自分なりにベタグランドのアンテナを除去した
2021-09-14 ベタグランドのアンテナを除去してデザインルールチェックも済ませた.
2021-09-14 ガーバファイルまで出力
2021-09-16 2u キーにスタビライザを適応
2021-09-21 Inventor バージョンに配慮
2021-09-21 Base を作成
2021-09-22 Inventor Board の作成
2021-09-24 人に見せる用のファイルを追加
2021-09-24 PDF データでええやんってなった。
2021-09-25 ピンヘッダno
2021-09-25 ピンヘッダの STEP ファイルを追加
2021-09-25 まだねじ穴斬ってない
2021-09-30 MISUMI で注文できるように調整。MC で削りだせるように調整
2021-10-28 hogehoge
2021-11-20 Base の微調整
2021-11-20 重大な修正 基板との干渉を解消
2022-10-20 hoge
